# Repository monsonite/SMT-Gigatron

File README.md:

# SMT-Gigatron
Gigatron implemented in SMT components

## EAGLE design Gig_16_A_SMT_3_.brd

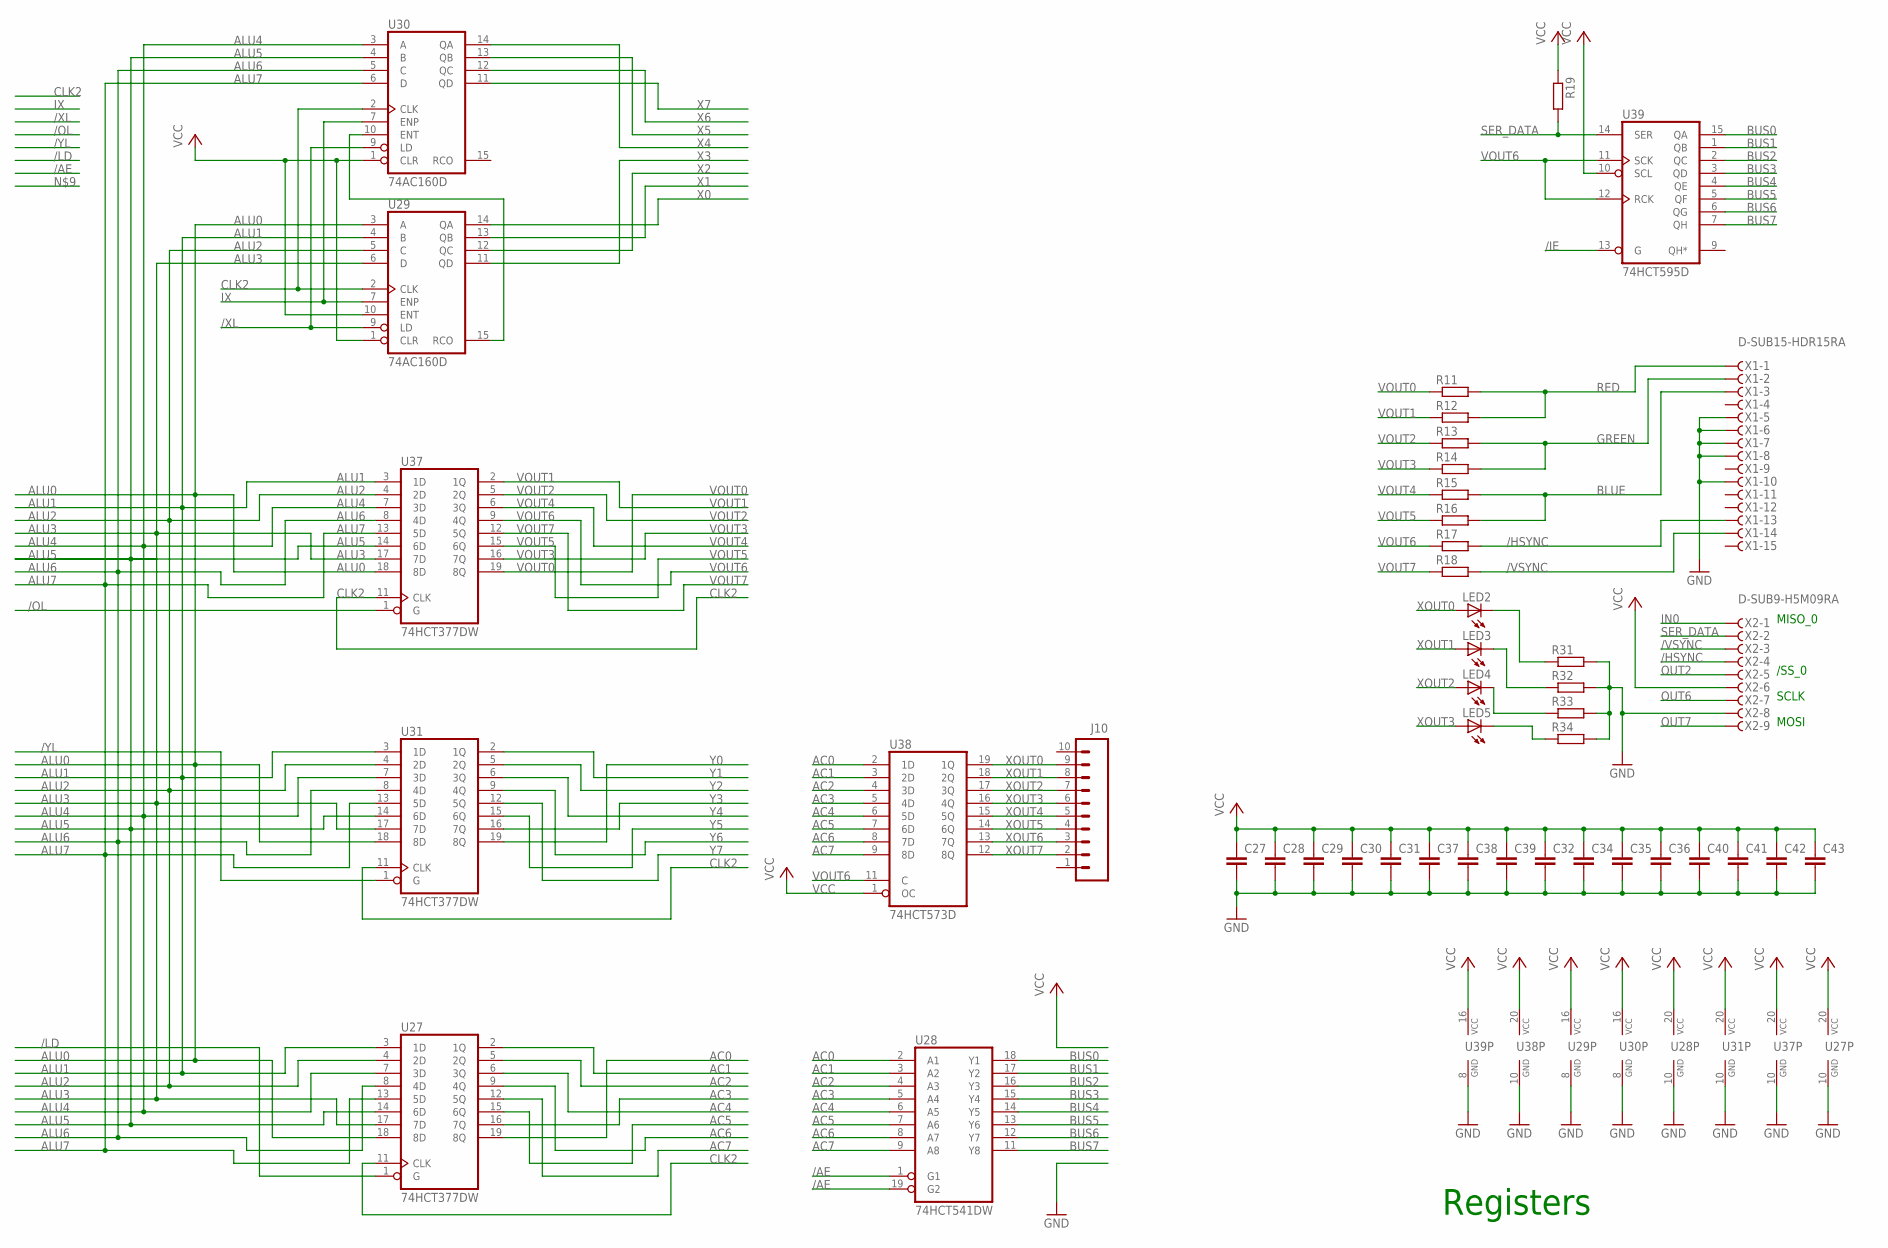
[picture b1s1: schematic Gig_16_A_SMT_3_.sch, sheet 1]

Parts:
C27, C28, C29, C30, C31, C32, C34, C35, C36, C37, C38, C39, C40, C41, C42, C43: RCL_C-EUC0603; RCL_C0603
J10: M10SILK_FEMALE_PTH; 1X10
LED2, LED3, LED4, LED5: LEDCHIPLED_0603; CHIPLED_0603
R11, R12, R13, R14, R15, R16, R17, R18, R19, R31, R32, R33, R34: R-EU_R0603; R0603
U27, U31, U37: 74HCT377DW; SO20W
U28: 74HCT541DW; SO20W
U29, U30: 74AC160D; SO16
U38: 74HCT573D; SO20W
U39: 74HCT595D; SO16
X1: D-SUB15-HDR15RA; HDR15RA
X2: D-SUB9-H5M09RA; H5M09RA

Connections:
/AE: U28.1 (G1), U28.19 (G2); also elsewhere on the board
/HSYNC: R17.2, X1.13, X2.4
/IE: U39.13 (G); also elsewhere on the board
/LD: U27.1 (G); also elsewhere on the board
/OL: U37.1 (G); also elsewhere on the board
/VSYNC: R18.2, X1.14, X2.3
/XL: U29.9 (LD), U30.9 (LD); also elsewhere on the board
/YL: U31.1 (G); also elsewhere on the board
AC0: U27.19 (8Q), U28.2 (A1), U38.2 (1D); also elsewhere on the board
AC1: U27.2 (1Q), U28.3 (A2), U38.3 (2D); also elsewhere on the board
AC2: U27.5 (2Q), U28.4 (A3), U38.4 (3D); also elsewhere on the board
AC3: U27.16 (7Q), U28.5 (A4), U38.5 (4D); also elsewhere on the board
AC4: U27.6 (3Q), U28.6 (A5), U38.6 (5D); also elsewhere on the board
AC5: U27.15 (6Q), U28.7 (A6), U38.7 (6D); also elsewhere on the board
AC6: U27.9 (4Q), U28.8 (A7), U38.8 (7D); also elsewhere on the board
AC7: U27.12 (5Q), U28.9 (A8), U38.9 (8D); also elsewhere on the board
ALU0: U27.18 (8D), U29.3 (A), U31.18 (8D), U37.18 (8D); also elsewhere on the board
ALU1: U27.3 (1D), U29.4 (B), U31.3 (1D), U37.3 (1D); also elsewhere on the board
ALU2: U27.4 (2D), U29.5 (C), U31.4 (2D), U37.4 (2D); also elsewhere on the board
ALU3: U27.17 (7D), U29.6 (D), U31.17 (7D), U37.17 (7D); also elsewhere on the board
ALU4: U27.7 (3D), U30.3 (A), U31.7 (3D), U37.7 (3D); also elsewhere on the board
ALU5: U27.14 (6D), U30.4 (B), U31.14 (6D), U37.14 (6D); also elsewhere on the board
ALU6: U27.8 (4D), U30.5 (C), U31.8 (4D), U37.8 (4D); also elsewhere on the board
ALU7: U27.13 (5D), U30.6 (D), U31.13 (5D), U37.13 (5D); also elsewhere on the board
BLUE: R15.2, R16.2, X1.3
BUS0: U28.18 (Y1), U39.15 (QA); also elsewhere on the board
BUS1: U28.17 (Y2), U39.1 (QB); also elsewhere on the board
BUS2: U28.16 (Y3), U39.2 (QC); also elsewhere on the board
BUS3: U28.15 (Y4), U39.3 (QD); also elsewhere on the board
BUS4: U28.14 (Y5), U39.4 (QE); also elsewhere on the board
BUS5: U28.13 (Y6), U39.5 (QF); also elsewhere on the board
BUS6: U28.12 (Y7), U39.6 (QG); also elsewhere on the board
BUS7: U28.11 (Y8), U39.7 (QH); also elsewhere on the board
CLK2: U27.11 (CLK), U29.2 (CLK), U30.2 (CLK), U31.11 (CLK), U37.11 (CLK); also elsewhere on the board
GND: C27.2, C28.2, C29.2, C30.2, C31.2, C32.2, C34.2, C35.2, C36.2, C37.2, C38.2, C39.2, C40.2, C41.2, C42.2, C43.2, R31.2, R32.2, R33.2, R34.2, U27.10 (GND), U28.10 (GND), U29.8 (GND), U30.8 (GND), U31.10 (GND), U37.10 (GND), U38.10 (GND), U39.8 (GND), X1.5, X1.6, X1.7, X1.8, X1.10, X2.8; also elsewhere on the board
GREEN: R13.2, R14.2, X1.2
IN0: X2.1; also elsewhere on the board
IX: U29.7 (ENP), U30.7 (ENP); also elsewhere on the board
unnamed: U29.15 (RCO), U30.10 (ENT)
unnamed: LED2.C, R31.1
unnamed: LED3.C, R32.1
unnamed: LED4.C, R33.1
unnamed: LED5.C, R34.1
OUT2: X2.5; also elsewhere on the board
OUT6: X2.7; also elsewhere on the board
OUT7: X2.9; also elsewhere on the board
RED: R11.2, R12.2, X1.1
SER_DATA: R19.2, U39.14 (SER), X2.2
VCC: C27.1, C28.1, C29.1, C30.1, C31.1, C32.1, C34.1, C35.1, C36.1, C37.1, C38.1, C39.1, C40.1, C41.1, C42.1, C43.1, R19.1, U27.20 (VCC), U28.20 (VCC), U29.1 (CLR), U29.10 (ENT), U29.16 (VCC), U30.1 (CLR), U30.16 (VCC), U31.20 (VCC), U37.20 (VCC), U38.1 (OC), U38.20 (VCC), U39.10 (SCL), U39.16 (VCC), X2.6; also elsewhere on the board
VOUT0: R11.1, U37.19 (8Q)
VOUT1: R12.1, U37.2 (1Q)
VOUT2: R13.1, U37.5 (2Q)
VOUT3: R14.1, U37.16 (7Q)
VOUT4: R15.1, U37.6 (3Q)
VOUT5: R16.1, U37.15 (6Q)
VOUT6: R17.1, U37.9 (4Q), U38.11 (C), U39.11 (SCK), U39.12 (RCK)
VOUT7: R18.1, U37.12 (5Q)
X0: U29.14 (QA); also elsewhere on the board
X1: U29.13 (QB); also elsewhere on the board
X2: U29.12 (QC); also elsewhere on the board
X3: U29.11 (QD); also elsewhere on the board
X4: U30.14 (QA); also elsewhere on the board
X5: U30.13 (QB); also elsewhere on the board
X6: U30.12 (QC); also elsewhere on the board
X7: U30.11 (QD); also elsewhere on the board
XOUT0: J10.9, LED2.A, U38.19 (1Q)
XOUT1: J10.8, LED3.A, U38.18 (2Q)
XOUT2: J10.7, LED4.A, U38.17 (3Q)
XOUT3: J10.6, LED5.A, U38.16 (4Q)
XOUT4: J10.5, U38.15 (5Q)
XOUT5: J10.4, U38.14 (6Q)
XOUT6: J10.3, U38.13 (7Q)
XOUT7: J10.2, U38.12 (8Q)
Y0: U31.19 (8Q); also elsewhere on the board
Y1: U31.2 (1Q); also elsewhere on the board
Y2: U31.5 (2Q); also elsewhere on the board
Y3: U31.16 (7Q); also elsewhere on the board
Y4: U31.6 (3Q); also elsewhere on the board
Y5: U31.15 (6Q); also elsewhere on the board
Y6: U31.9 (4Q); also elsewhere on the board
Y7: U31.12 (5Q); also elsewhere on the board

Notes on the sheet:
Registers
MISO_0
/SS_0
SCLK
MOSI

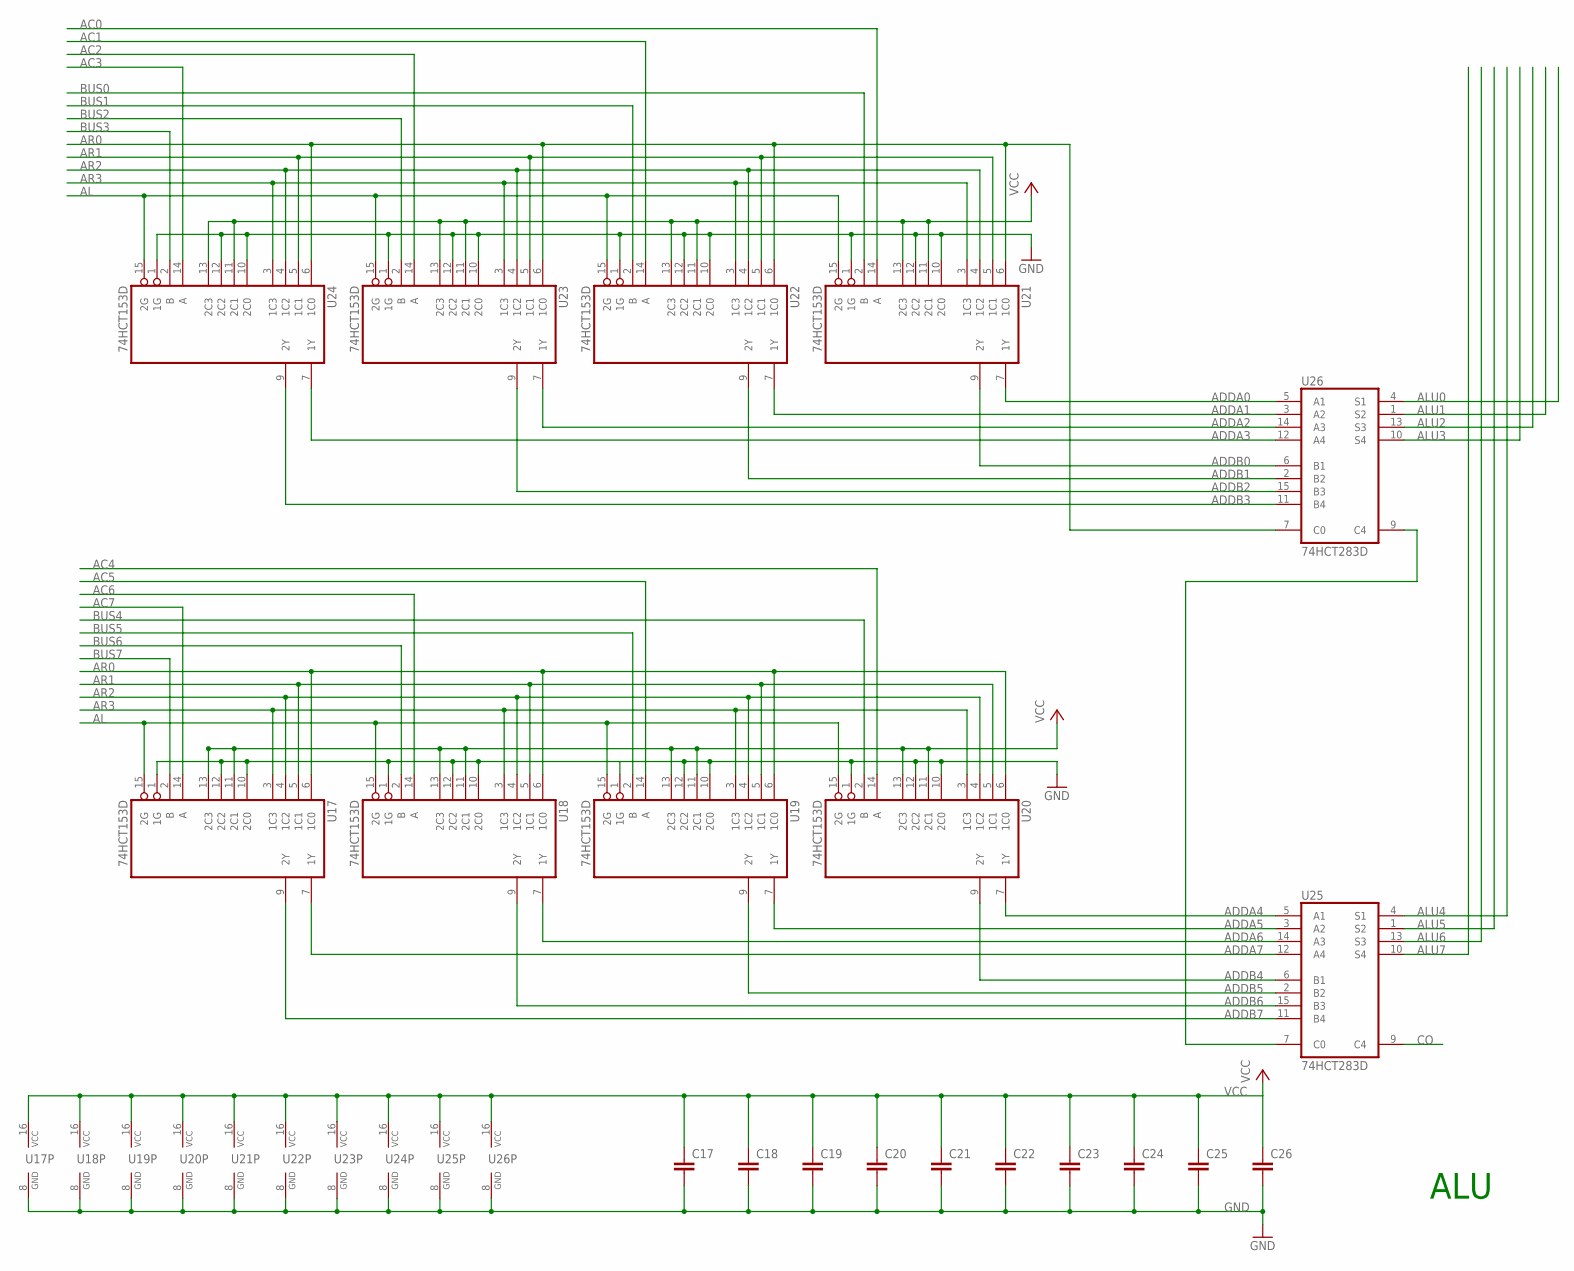
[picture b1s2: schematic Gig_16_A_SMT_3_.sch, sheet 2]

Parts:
C17, C18, C19, C20, C21, C22, C23, C24, C25, C26: RCL_C-EUC0603; RCL_C0603
U17, U18, U19, U20, U21, U22, U23, U24: 74HCT153D; SO16
U25, U26: 74HCT283D; SO16

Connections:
AC0: U21.14 (A); also elsewhere on the board
AC1: U22.14 (A); also elsewhere on the board
AC2: U23.14 (A); also elsewhere on the board
AC3: U24.14 (A); also elsewhere on the board
AC4: U20.14 (A); also elsewhere on the board
AC5: U19.14 (A); also elsewhere on the board
AC6: U18.14 (A); also elsewhere on the board
AC7: U17.14 (A); also elsewhere on the board
ADDA0: U21.7 (1Y), U26.5 (A1)
ADDA1: U22.7 (1Y), U26.3 (A2)
ADDA2: U23.7 (1Y), U26.14 (A3)
ADDA3: U24.7 (1Y), U26.12 (A4)
ADDA4: U20.7 (1Y), U25.5 (A1)
ADDA5: U19.7 (1Y), U25.3 (A2)
ADDA6: U18.7 (1Y), U25.14 (A3)
ADDA7: U17.7 (1Y), U25.12 (A4)
ADDB0: U21.9 (2Y), U26.6 (B1)
ADDB1: U22.9 (2Y), U26.2 (B2)
ADDB2: U23.9 (2Y), U26.15 (B3)
ADDB3: U24.9 (2Y), U26.11 (B4)
ADDB4: U20.9 (2Y), U25.6 (B1)
ADDB5: U19.9 (2Y), U25.2 (B2)
ADDB6: U18.9 (2Y), U25.15 (B3)
ADDB7: U17.9 (2Y), U25.11 (B4)
AL: U17.15 (2G), U18.15 (2G), U19.15 (2G), U20.15 (2G), U21.15 (2G), U22.15 (2G), U23.15 (2G), U24.15 (2G); also elsewhere on the board
ALU0: U26.4 (S1); also elsewhere on the board
ALU1: U26.1 (S2); also elsewhere on the board
ALU2: U26.13 (S3); also elsewhere on the board
ALU3: U26.10 (S4); also elsewhere on the board
ALU4: U25.4 (S1); also elsewhere on the board
ALU5: U25.1 (S2); also elsewhere on the board
ALU6: U25.13 (S3); also elsewhere on the board
ALU7: U25.10 (S4); also elsewhere on the board
AR0: U17.6 (1C0), U18.6 (1C0), U19.6 (1C0), U20.6 (1C0), U21.6 (1C0), U22.6 (1C0), U23.6 (1C0), U24.6 (1C0), U26.7 (C0); also elsewhere on the board
AR1: U17.5 (1C1), U18.5 (1C1), U19.5 (1C1), U20.5 (1C1), U21.5 (1C1), U22.5 (1C1), U23.5 (1C1), U24.5 (1C1); also elsewhere on the board
AR2: U17.4 (1C2), U18.4 (1C2), U19.4 (1C2), U20.4 (1C2), U21.4 (1C2), U22.4 (1C2), U23.4 (1C2), U24.4 (1C2); also elsewhere on the board
AR3: U17.3 (1C3), U18.3 (1C3), U19.3 (1C3), U20.3 (1C3), U21.3 (1C3), U22.3 (1C3), U23.3 (1C3), U24.3 (1C3); also elsewhere on the board
BUS0: U21.2 (B); also elsewhere on the board
BUS1: U22.2 (B); also elsewhere on the board
BUS2: U23.2 (B); also elsewhere on the board
BUS3: U24.2 (B); also elsewhere on the board
BUS4: U20.2 (B); also elsewhere on the board
BUS5: U19.2 (B); also elsewhere on the board
BUS6: U18.2 (B); also elsewhere on the board
BUS7: U17.2 (B); also elsewhere on the board
CO: U25.9 (C4); also elsewhere on the board
GND: C17.2, C18.2, C19.2, C20.2, C21.2, C22.2, C23.2, C24.2, C25.2, C26.2, U17.1 (1G), U17.8 (GND), U17.10 (2C0), U17.12 (2C2), U18.1 (1G), U18.8 (GND), U18.10 (2C0), U18.12 (2C2), U19.1 (1G), U19.8 (GND), U19.10 (2C0), U19.12 (2C2), U20.1 (1G), U20.8 (GND), U20.10 (2C0), U20.12 (2C2), U21.1 (1G), U21.8 (GND), U21.10 (2C0), U21.12 (2C2), U22.1 (1G), U22.8 (GND), U22.10 (2C0), U22.12 (2C2), U23.1 (1G), U23.8 (GND), U23.10 (2C0), U23.12 (2C2), U24.1 (1G), U24.8 (GND), U24.10 (2C0), U24.12 (2C2), U25.8 (GND), U26.8 (GND); also elsewhere on the board
unnamed: U25.7 (C0), U26.9 (C4)
VCC: C17.1, C18.1, C19.1, C20.1, C21.1, C22.1, C23.1, C24.1, C25.1, C26.1, U17.11 (2C1), U17.13 (2C3), U17.16 (VCC), U18.11 (2C1), U18.13 (2C3), U18.16 (VCC), U19.11 (2C1), U19.13 (2C3), U19.16 (VCC), U20.11 (2C1), U20.13 (2C3), U20.16 (VCC), U21.11 (2C1), U21.13 (2C3), U21.16 (VCC), U22.11 (2C1), U22.13 (2C3), U22.16 (VCC), U23.11 (2C1), U23.13 (2C3), U23.16 (VCC), U24.11 (2C1), U24.13 (2C3), U24.16 (VCC), U25.16 (VCC), U26.16 (VCC); also elsewhere on the board

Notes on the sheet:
ALU

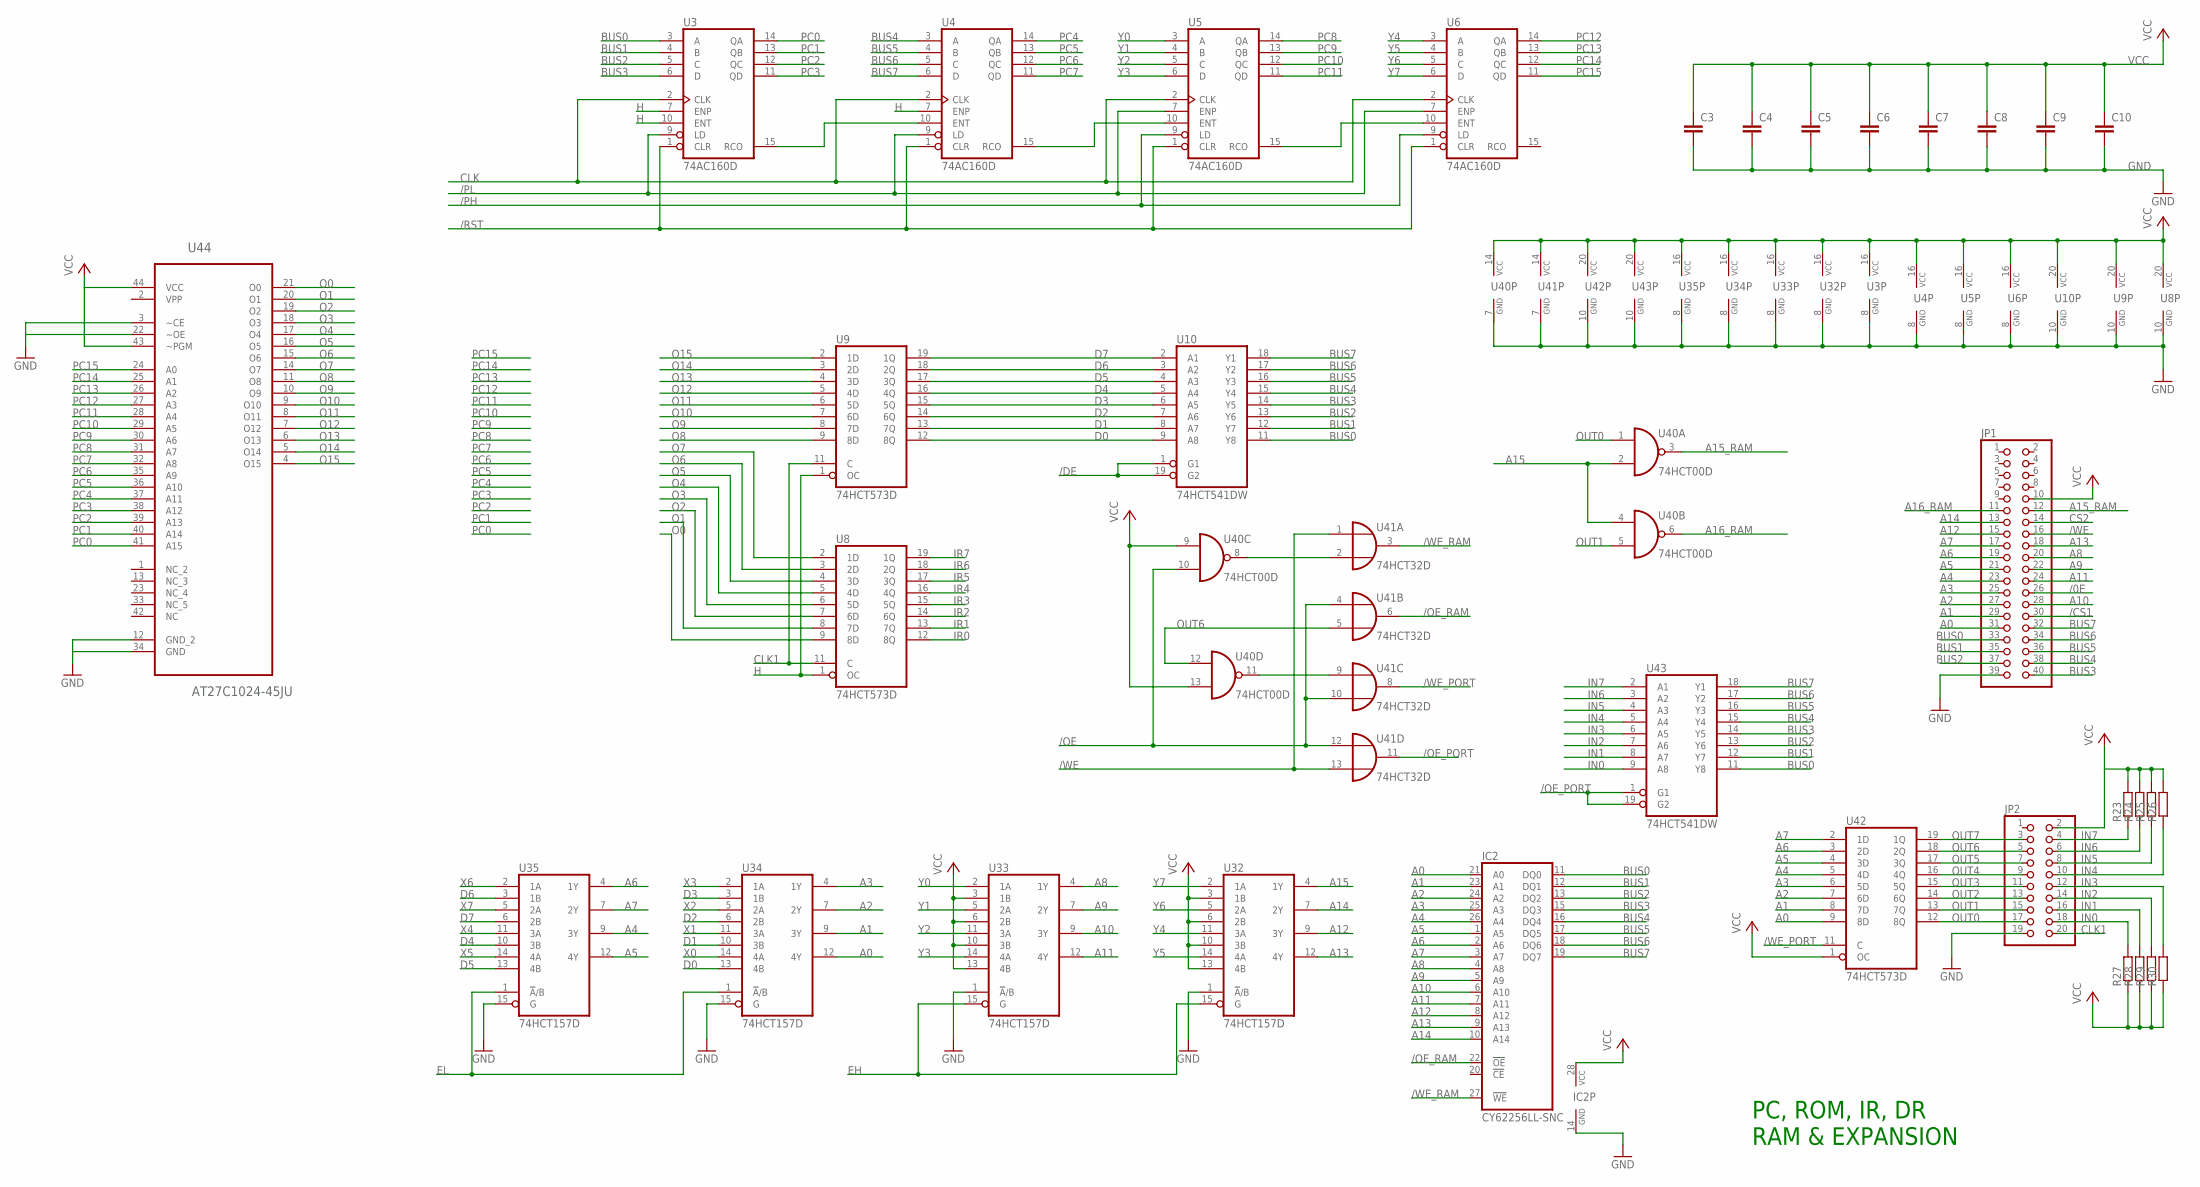
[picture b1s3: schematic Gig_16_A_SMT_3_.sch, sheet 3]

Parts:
C3, C4, C5, C6, C7, C8, C9, C10: RCL_C-EUC0603; RCL_C0603
IC2: CY62256LL-SNC; SOJ28/3
JP1: PINHD-2X20; 2X20
JP2: PINHD-2X10; 2X10
R23, R24, R25, R26, R27, R28, R29, R30: R-EU_R0603; R0603
U3, U4, U5, U6: 74AC160D; SO16
U8, U9, U42: 74HCT573D; SO20W
U10, U43: 74HCT541DW; SO20W
U32, U33, U34, U35: 74HCT157D; SO16
U40: 74HCT00D; SO14
U41: 74HCT32D; SO14
U44: AT27C1024-45JU; PLCC127P1752X1752X457-44N

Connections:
/0E: JP1.26
/CS1: JP1.30
/DE: U10.1 (G1), U10.19 (G2); also elsewhere on the board
/OE: U40.10 (I1), U41.4 (I0), U41.10 (I1), U41.12 (I0); also elsewhere on the board
/OE_PORT: U41.11 (O), U43.1 (G1), U43.19 (G2)
/OE_RAM: IC2.22 (!OE), U41.6 (O)
/PH: U5.9 (LD), U6.9 (LD); also elsewhere on the board
/PL: U3.9 (LD), U4.9 (LD), U5.7 (ENP), U6.7 (ENP); also elsewhere on the board
/RST: U3.1 (CLR), U4.1 (CLR), U5.1 (CLR), U6.1 (CLR); also elsewhere on the board
/WE: JP1.16, U41.1 (I0), U41.13 (I1); also elsewhere on the board
/WE_PORT: U41.8 (O), U42.11 (C)
/WE_RAM: U41.3 (O)
A0: IC2.21 (A0), JP1.31, U34.12 (4Y), U42.9 (8D)
A1: IC2.23 (A1), JP1.29, U34.9 (3Y), U42.8 (7D)
A2: IC2.24 (A2), JP1.27, U34.7 (2Y), U42.7 (6D)
A3: IC2.25 (A3), JP1.25, U34.4 (1Y), U42.6 (5D)
A4: IC2.26 (A4), JP1.23, U35.9 (3Y), U42.5 (4D)
A5: IC2.1 (A5), JP1.21, U35.12 (4Y), U42.4 (3D)
A6: IC2.2 (A6), JP1.19, U35.4 (1Y), U42.3 (2D)
A7: IC2.3 (A7), JP1.17, U35.7 (2Y), U42.2 (1D)
A8: IC2.4 (A8), JP1.20, U33.4 (1Y)
A9: IC2.5 (A9), JP1.22, U33.7 (2Y)
A10: IC2.6 (A10), JP1.28, U33.9 (3Y)
A11: IC2.7 (A11), JP1.24, U33.12 (4Y)
A12: IC2.8 (A12), JP1.15, U32.9 (3Y)
A13: IC2.9 (A13), JP1.18, U32.12 (4Y)
A14: IC2.10 (A14), JP1.13, U32.7 (2Y)
A15: U32.4 (1Y), U40.2 (I1), U40.4 (I0)
A15_RAM: JP1.12, U40.3 (O)
A16_RAM: JP1.11, U40.6 (O)
BUS0: JP1.33, U3.3 (A), U10.11 (Y8), U43.11 (Y8); also elsewhere on the board
BUS1: JP1.35, U3.4 (B), U10.12 (Y7), U43.12 (Y7); also elsewhere on the board
BUS2: JP1.37, U3.5 (C), U10.13 (Y6), U43.13 (Y6); also elsewhere on the board
BUS3: JP1.40, U3.6 (D), U10.14 (Y5), U43.14 (Y5); also elsewhere on the board
BUS4: JP1.38, U4.3 (A), U10.15 (Y4), U43.15 (Y4); also elsewhere on the board
BUS5: JP1.36, U4.4 (B), U10.16 (Y3), U43.16 (Y3); also elsewhere on the board
BUS6: JP1.34, U4.5 (C), U10.17 (Y2), U43.17 (Y2); also elsewhere on the board
BUS7: JP1.32, U4.6 (D), U10.18 (Y1), U43.18 (Y1); also elsewhere on the board
CLK: U3.2 (CLK), U4.2 (CLK), U5.2 (CLK), U6.2 (CLK)
CLK1: JP2.20, U8.11 (C), U9.11 (C); also elsewhere on the board
CS2: JP1.14
D0: U9.12 (8Q), U10.9 (A8), U34.13 (4B)
D1: U9.13 (7Q), U10.8 (A7), U34.10 (3B)
D2: U9.14 (6Q), U10.7 (A6), U34.6 (2B)
D3: U9.15 (5Q), U10.6 (A5), U34.3 (1B)
D4: U9.16 (4Q), U10.5 (A4), U35.10 (3B)
D5: U9.17 (3Q), U10.4 (A3), U35.13 (4B)
D6: U9.18 (2Q), U10.3 (A2), U35.3 (1B)
D7: U9.19 (1Q), U10.2 (A1), U35.6 (2B)
EH: U32.15 (G), U33.15 (G); also elsewhere on the board
EL: U34.1 (!A!/B), U35.1 (!A!/B); also elsewhere on the board
GND: C3.2, C4.2, C5.2, C6.2, C7.2, C8.2, C9.2, C10.2, IC2.14 (GND), JP1.39, JP2.19, U3.8 (GND), U4.8 (GND), U5.8 (GND), U6.8 (GND), U8.10 (GND), U9.10 (GND), U10.10 (GND), U32.1 (!A!/B), U32.8 (GND), U33.1 (!A!/B), U33.8 (GND), U34.8 (GND), U34.15 (G), U35.8 (GND), U35.15 (G), U40.7 (GND), U41.7 (GND), U42.10 (GND), U43.10 (GND), U44.3 (~CE), U44.12 (GND_2), U44.22 (~OE), U44.34 (GND); also elsewhere on the board
H: U3.7 (ENP), U3.10 (ENT), U4.7 (ENP), U8.1 (OC), U9.1 (OC)
IN0: JP2.18, R27.2, U43.9 (A8); also elsewhere on the board
IN1: JP2.16, R28.2, U43.8 (A7)
IN2: JP2.14, R29.2, U43.7 (A6)
IN3: JP2.12, R30.2, U43.6 (A5)
IN4: JP2.10, R26.1, U43.5 (A4)
IN5: JP2.8, R25.1, U43.4 (A3)
IN6: JP2.6, R24.1, U43.3 (A2)
IN7: JP2.4, R23.1, U43.2 (A1)
IR0: U8.12 (8Q); also elsewhere on the board
IR1: U8.13 (7Q); also elsewhere on the board
IR2: U8.14 (6Q); also elsewhere on the board
IR3: U8.15 (5Q); also elsewhere on the board
IR4: U8.16 (4Q); also elsewhere on the board
IR5: U8.17 (3Q); also elsewhere on the board
IR6: U8.18 (2Q); also elsewhere on the board
IR7: U8.19 (1Q); also elsewhere on the board
unnamed: U40.8 (O), U41.2 (I1)
unnamed: U40.11 (O), U41.9 (I0)
unnamed: U3.15 (RCO), U4.10 (ENT)
unnamed: U4.15 (RCO), U5.10 (ENT)
unnamed: U5.15 (RCO), U6.10 (ENT)
O0: U8.9 (8D), U44.21 (O0)
O1: U8.8 (7D), U44.20 (O1)
O2: U8.7 (6D), U44.19 (O2)
O3: U8.6 (5D), U44.18 (O3)
O4: U8.5 (4D), U44.17 (O4)
O5: U8.4 (3D), U44.16 (O5)
O6: U8.3 (2D), U44.15 (O6)
O7: U8.2 (1D), U44.14 (O7)
O8: U9.9 (8D), U44.11 (O8)
O9: U9.8 (7D), U44.10 (O9)
O10: U9.7 (6D), U44.9 (O10)
O11: U9.6 (5D), U44.8 (O11)
O12: U9.5 (4D), U44.7 (O12)
O13: U9.4 (3D), U44.6 (O13)
O14: U9.3 (2D), U44.5 (O14)
O15: U9.2 (1D), U44.4 (O15)
OUT0: JP2.17, U40.1 (I0), U42.12 (8Q)
OUT1: JP2.15, U40.5 (I1), U42.13 (7Q)
OUT2: JP2.13, U42.14 (6Q); also elsewhere on the board
OUT3: JP2.11, U42.15 (5Q)
OUT4: JP2.9, U42.16 (4Q)
OUT5: JP2.7, U42.17 (3Q)
OUT6: JP2.5, U40.12 (I0), U41.5 (I1), U42.18 (2Q); also elsewhere on the board
OUT7: JP2.3, U42.19 (1Q); also elsewhere on the board
PC0: U3.14 (QA)
PC1: U3.13 (QB)
PC2: U3.12 (QC)
PC3: U3.11 (QD)
PC4: U4.14 (QA)
PC5: U4.13 (QB)
PC6: U4.12 (QC)
PC7: U4.11 (QD)
PC8: U5.14 (QA)
PC9: U5.13 (QB)
PC10: U5.12 (QC)
PC11: U5.11 (QD)
PC12: U6.14 (QA)
PC13: U6.13 (QB)
PC14: U6.12 (QC)
PC15: U6.11 (QD)
VCC: C3.1, C4.1, C5.1, C6.1, C7.1, C8.1, C9.1, C10.1, IC2.28 (VCC), JP1.10, JP2.2, R23.2, R24.2, R25.2, R26.2, R27.1, R28.1, R29.1, R30.1, U3.16 (VCC), U4.16 (VCC), U5.16 (VCC), U6.16 (VCC), U8.20 (VCC), U9.20 (VCC), U10.20 (VCC), U32.3 (1B), U32.6 (2B), U32.10 (3B), U32.13 (4B), U32.16 (VCC), U33.3 (1B), U33.6 (2B), U33.10 (3B), U33.13 (4B), U33.16 (VCC), U34.16 (VCC), U35.16 (VCC), U40.9 (I0), U40.13 (I1), U40.14 (VCC), U41.14 (VCC), U42.1 (OC), U42.20 (VCC), U43.20 (VCC), U44.43 (~PGM), U44.44 (VCC); also elsewhere on the board
VPP: U44.2 (VPP)
X0: U34.14 (4A); also elsewhere on the board
X1: U34.11 (3A); also elsewhere on the board
X2: U34.5 (2A); also elsewhere on the board
X3: U34.2 (1A); also elsewhere on the board
X4: U35.11 (3A); also elsewhere on the board
X5: U35.14 (4A); also elsewhere on the board
X6: U35.2 (1A); also elsewhere on the board
X7: U35.5 (2A); also elsewhere on the board
Y0: U5.3 (A), U33.2 (1A); also elsewhere on the board
Y1: U5.4 (B), U33.5 (2A); also elsewhere on the board
Y2: U5.5 (C), U33.11 (3A); also elsewhere on the board
Y3: U5.6 (D), U33.14 (4A); also elsewhere on the board
Y4: U6.3 (A), U32.11 (3A); also elsewhere on the board
Y5: U6.4 (B), U32.14 (4A); also elsewhere on the board
Y6: U6.5 (C), U32.5 (2A); also elsewhere on the board
Y7: U6.6 (D), U32.2 (1A); also elsewhere on the board

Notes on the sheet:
PC, ROM, IR, DR RAM & EXPANSION

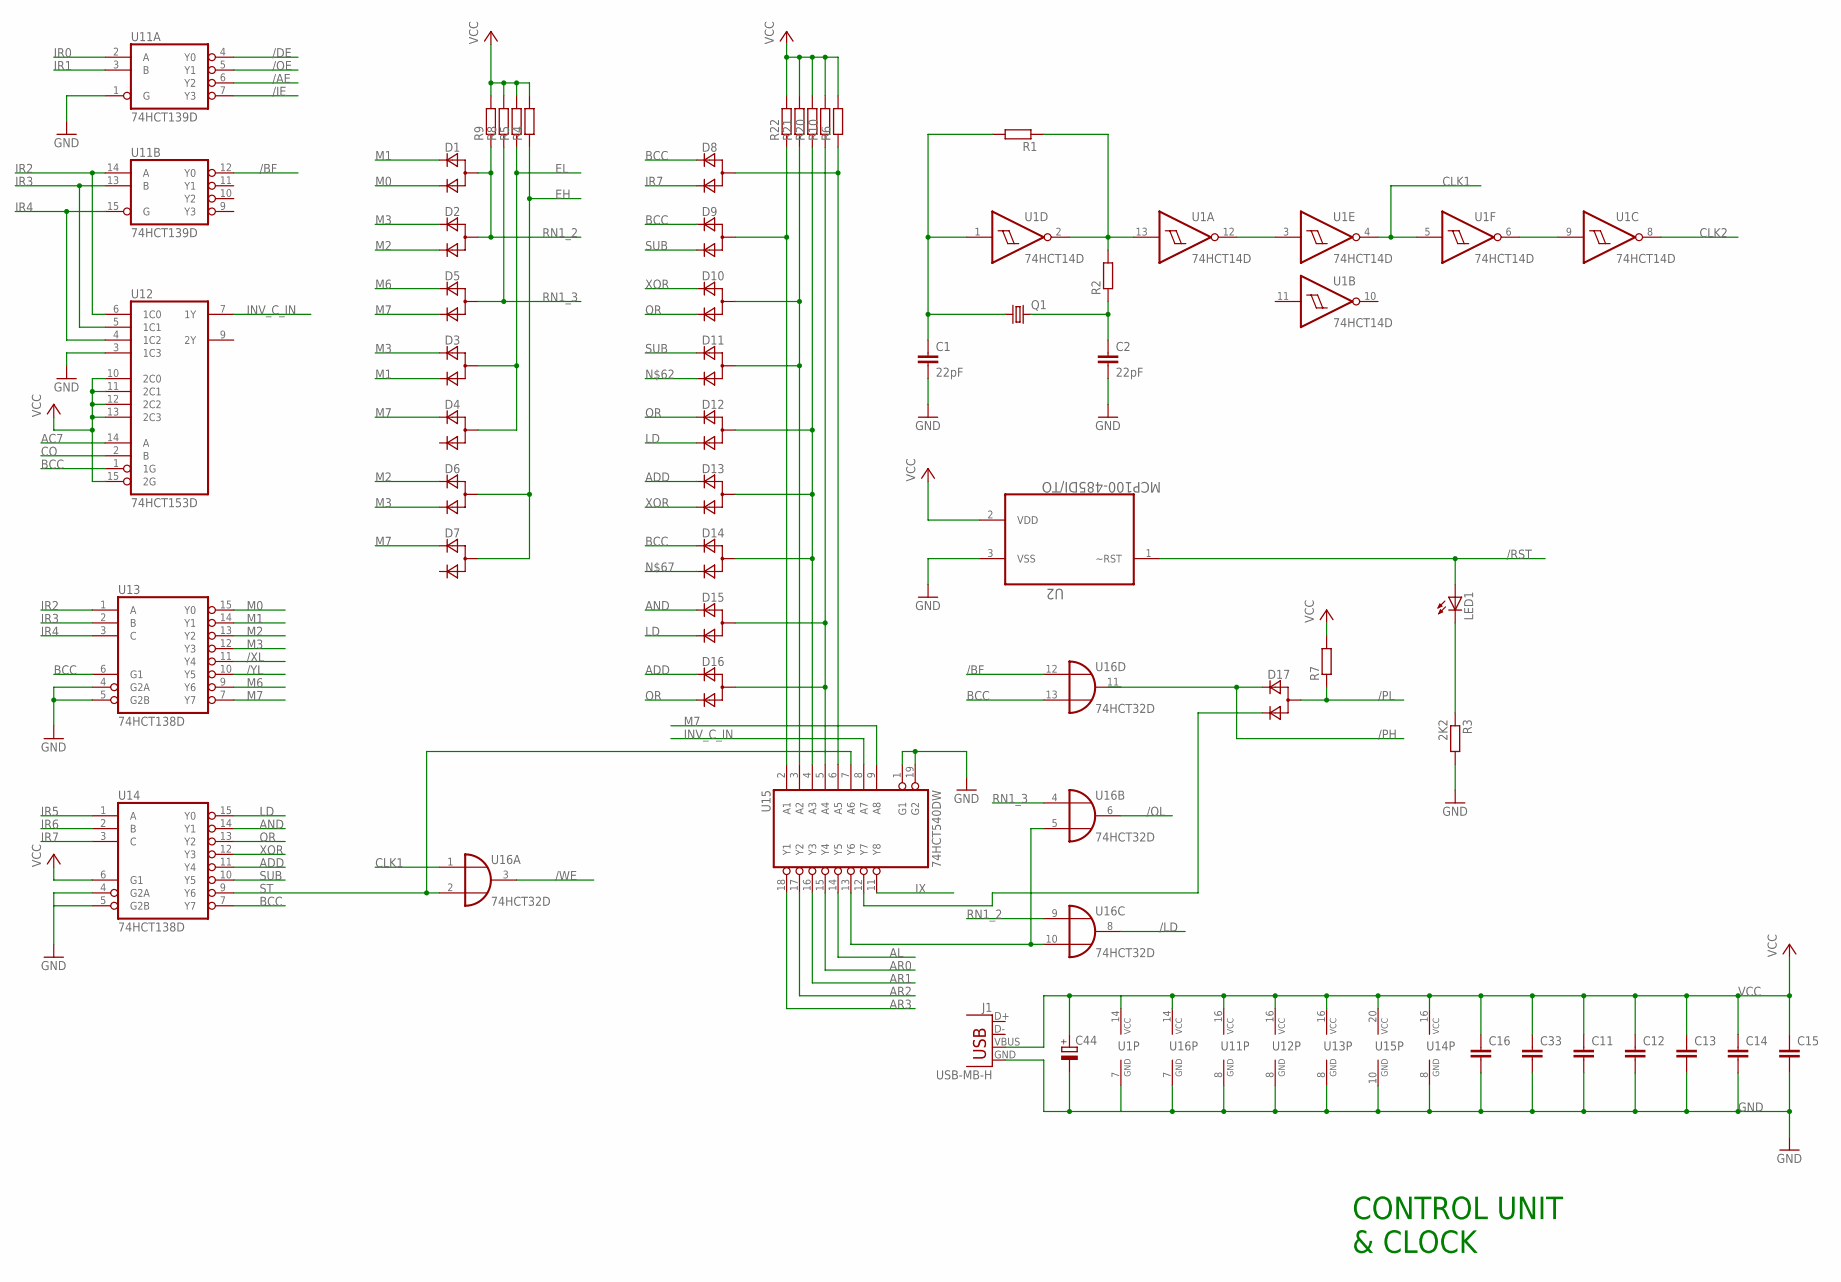
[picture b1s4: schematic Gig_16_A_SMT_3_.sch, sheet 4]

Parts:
C1, C2: 22pF; RCL_C0603
C11, C13, C14, C15, C16, C33: RCL_C-EUC0603; RCL_C0603
C12: RCL_C-EUC0603K; RCL_C0603K
C44: CPOL-EUE5-8.5; E5-8,5
D1, D2, D3, D4, D5, D6, D7, D8, D9, D10, D11, D12, D13, D14, D15, D16, D17: D_2CSOT23; SOT-23
J1: USB-MB-H
LED1: LED_LEDCHIPLED_0603; LED_CHIPLED_0603
Q1: CRYSTALHC49S; HC49/S
R1, R2, R4, R5, R6, R7, R8, R9, R10, R20, R21, R22: R-EU_R0603; R0603
R3: 2K2; R0603
U1: 74HCT14D; SO14
U2: MCP100-485DI/TO; TO127P254X495-3
U11: 74HCT139D; SO16
U12: 74HCT153D; SO16
U13, U14: 74HCT138D; SO16
U15: 74HCT540DW; SO20W
U16: 74HCT32D; SO14

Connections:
/AE: U11.6 (Y2); also elsewhere on the board
/BF: U11.12 (Y0), U16.12 (I0)
/DE: U11.4 (Y0); also elsewhere on the board
/IE: U11.7 (Y3); also elsewhere on the board
/LD: U16.8 (O); also elsewhere on the board
/OE: U11.5 (Y1); also elsewhere on the board
/OL: U16.6 (O); also elsewhere on the board
/PH: D17.2 (C1); also elsewhere on the board
/PL: D17.1 (A), R7.1; also elsewhere on the board
/RST: LED1.A, U2.1 (~RST); also elsewhere on the board
/WE: U16.3 (O); also elsewhere on the board
/XL: U13.11 (Y4); also elsewhere on the board
/YL: U13.10 (Y5); also elsewhere on the board
AC7: U12.14 (A); also elsewhere on the board
ADD: D13.2 (C1), D16.2 (C1), U14.11 (Y4)
AL: U15.14 (Y5); also elsewhere on the board
AND: D15.2 (C1), U14.14 (Y1)
AR0: U15.15 (Y4); also elsewhere on the board
AR1: U15.16 (Y3); also elsewhere on the board
AR2: U15.17 (Y2); also elsewhere on the board
AR3: U15.18 (Y1); also elsewhere on the board
BCC: D8.2 (C1), D9.2 (C1), D14.2 (C1), U12.1 (1G), U13.6 (G1), U14.7 (Y7), U16.13 (I1)
CLK1: U1.4 (O), U1.5 (I), U16.1 (I0); also elsewhere on the board
CLK2: U1.8 (O); also elsewhere on the board
CO: U12.2 (B); also elsewhere on the board
EH: D6.1 (A), D7.1 (A), R4.1; also elsewhere on the board
EL: D3.1 (A), D4.1 (A), R5.1; also elsewhere on the board
GND: C1.2, C2.2, C11.2, C12.2, C13.2, C14.2, C15.2, C16.2, C33.2, C44.-, J1.GND, R3.2, U1.7 (GND), U2.3 (VSS), U11.1 (G), U11.8 (GND), U12.3 (1C3), U12.8 (GND), U13.4 (G2A), U13.5 (G2B), U13.8 (GND), U14.4 (G2A), U14.5 (G2B), U14.8 (GND), U15.1 (G1), U15.10 (GND), U15.19 (G2), U16.7 (GND); also elsewhere on the board
INV_C_IN: U12.7 (1Y), U15.8 (A7)
IR0: U11.2 (A); also elsewhere on the board
IR1: U11.3 (B); also elsewhere on the board
IR2: U11.14 (A), U12.6 (1C0), U13.1 (A); also elsewhere on the board
IR3: U11.13 (B), U12.5 (1C1), U13.2 (B); also elsewhere on the board
IR4: U11.15 (G), U12.4 (1C2), U13.3 (C); also elsewhere on the board
IR5: U14.1 (A); also elsewhere on the board
IR6: U14.2 (B); also elsewhere on the board
IR7: D8.3 (C2), U14.3 (C); also elsewhere on the board
IX: U15.11 (Y8); also elsewhere on the board
LD: D12.3 (C2), D15.3 (C2), U14.15 (Y0)
M0: D1.3 (C2), U13.15 (Y0)
M1: D1.2 (C1), D3.3 (C2), U13.14 (Y1)
M2: D2.3 (C2), D6.2 (C1), U13.13 (Y2)
M3: D2.2 (C1), D3.2 (C1), D6.3 (C2), U13.12 (Y3)
M6: D5.2 (C1), U13.9 (Y6)
M7: D4.2 (C1), D5.3 (C2), D7.2 (C1), U13.7 (Y7), U15.9 (A8)
unnamed: D8.1 (A), R6.1, U15.6 (A5)
unnamed: C1.1, Q1.1, R1.2, U1.1 (I)
unnamed: D17.3 (C2), U15.12 (Y7)
unnamed: C2.1, Q1.2, R2.1
unnamed: R1.1, R2.2, U1.2 (O), U1.13 (I)
unnamed: D9.1 (A), R22.1, U15.2 (A1)
unnamed: D10.1 (A), D11.1 (A), R21.1, U15.3 (A2)
unnamed: D12.1 (A), D13.1 (A), D14.1 (A), R20.1, U15.4 (A3)
unnamed: D15.1 (A), D16.1 (A), R10.1, U15.5 (A4)
unnamed: U1.3 (I), U1.12 (O)
unnamed: U15.13 (Y6), U16.5 (I1), U16.10 (I1)
unnamed: LED1.C, R3.1
unnamed: U1.6 (O), U1.9 (I)
OR: D10.3 (C2), D12.2 (C1), D16.3 (C2), U14.13 (Y2)
RN1_2: D1.1 (A), D2.1 (A), R9.1, U16.9 (I0)
RN1_3: D5.1 (A), R8.1, U16.4 (I0)
ST: U14.9 (Y6), U15.7 (A6), U16.2 (I1)
SUB: D9.3 (C2), D11.2 (C1), U14.10 (Y5)
VCC: C11.1, C12.1, C13.1, C14.1, C15.1, C16.1, C33.1, C44.+, J1.VBUS, R4.2, R5.2, R6.2, R7.2, R8.2, R9.2, R10.2, R20.2, R21.2, R22.2, U1.14 (VCC), U2.2 (VDD), U11.16 (VCC), U12.10 (2C0), U12.11 (2C1), U12.12 (2C2), U12.13 (2C3), U12.15 (2G), U12.16 (VCC), U13.16 (VCC), U14.6 (G1), U14.16 (VCC), U15.20 (VCC), U16.14 (VCC); also elsewhere on the board
XOR: D10.2 (C1), D13.3 (C2), U14.12 (Y3)

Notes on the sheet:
CONTROL UNIT & CLOCK

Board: 4 copper layers, 150 parts (0 on the bottom side), 216 nets, no tracks yet.

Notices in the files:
parts and their libraries:
SparkFun-Connectors: Licensing: Creative Commons ShareAlike 4.0 International - https://creativecommons.org/licenses/by-sa/4.0
